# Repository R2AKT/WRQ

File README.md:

License addendum - https://github.com/R2AKT/WRQ/blob/main/Addendum.txt

# WRQ

Wait state insertion module. For Mega-80 (Mega-580) DIY 8-bit micro-computer - https://github.com/R2AKT/Mega-80.

Generation of a CPU module 'Wait' signal upon request from a slow device.

Status: Under testing.

Модуль задержки. Для самодельной 8-битной микро-ЭВМ - https://github.com/R2AKT/Mega-80.

Генерация по запросу от медленного устройства сигнала торможения процессорного модуля.

Статус: В стадии тестирования.

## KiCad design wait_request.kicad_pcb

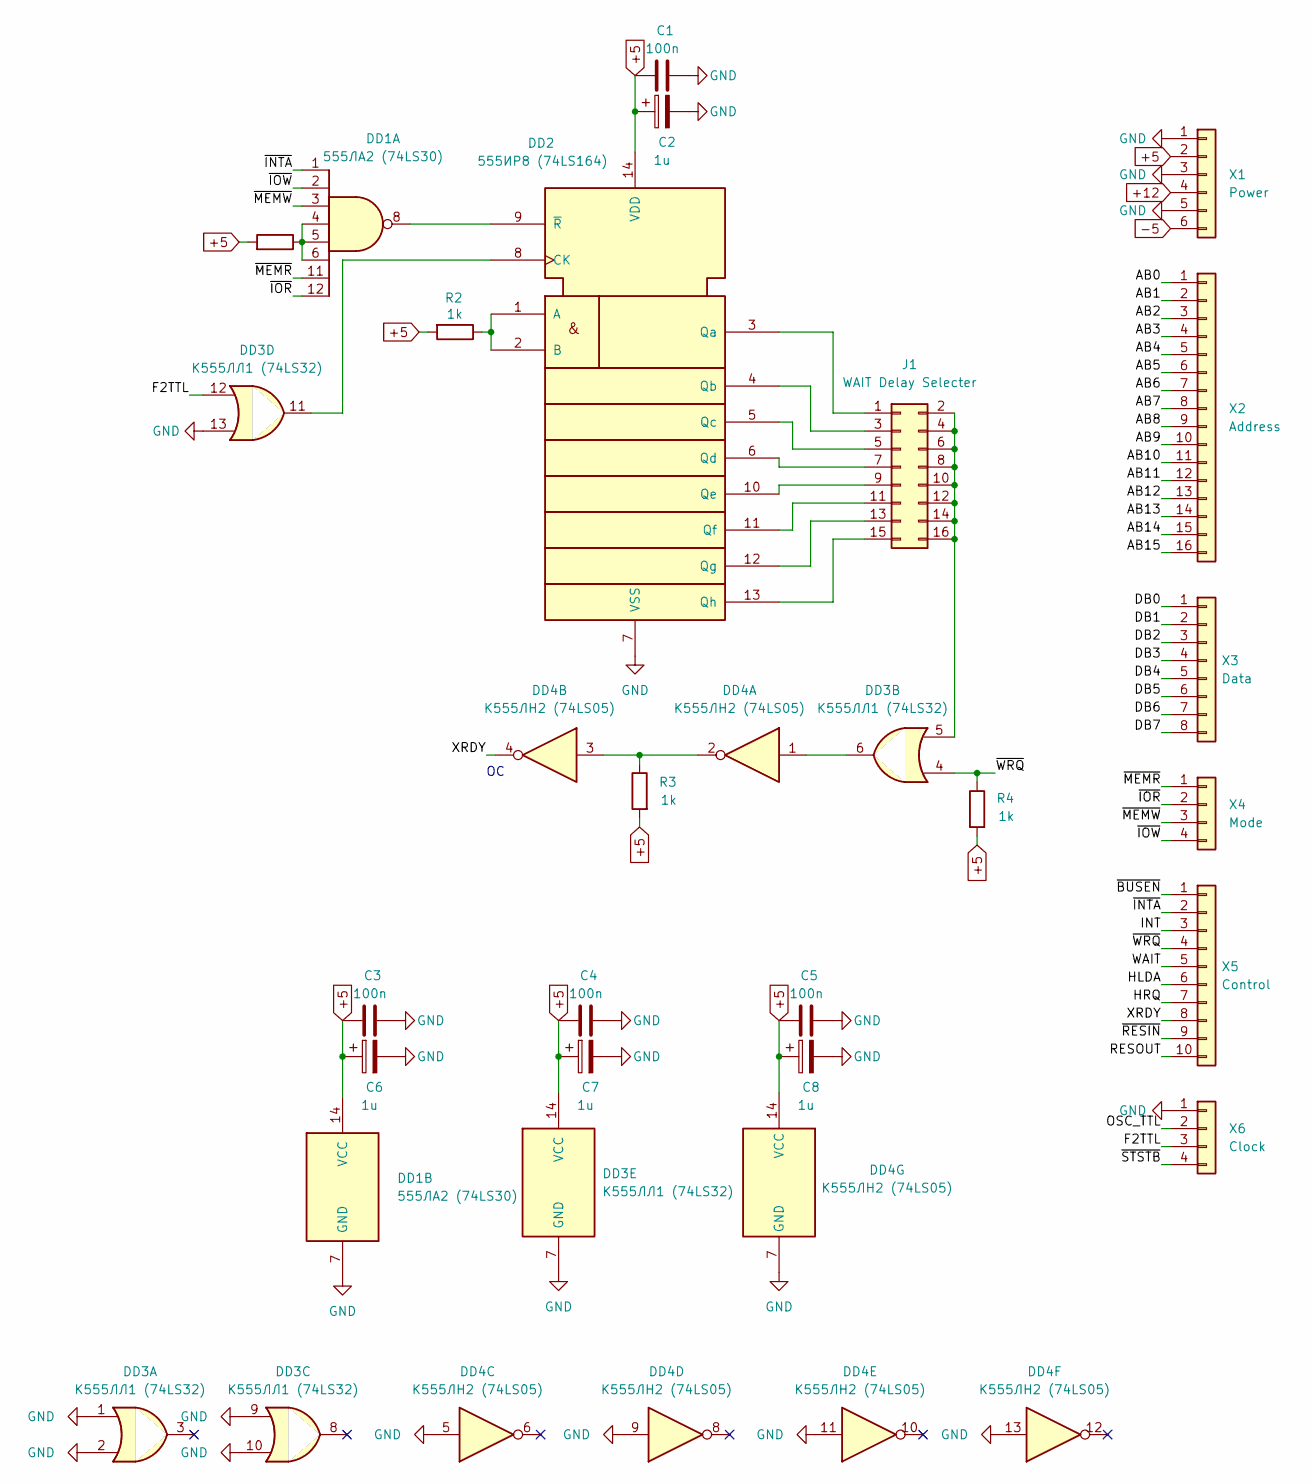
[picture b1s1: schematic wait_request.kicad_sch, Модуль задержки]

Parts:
C1, C3, C4, C5: 100n; C_0805_2012Metric_Pad1.18x1.45mm_HandSolder
C2, C6, C7, C8: 1u; CP_EIA-3216-18_Kemet-A_Pad1.58x1.35mm_HandSolder
DD1: 555ЛА2 (74LS30); DIP-14_W7.62mm_Socket_LongPads
DD2: 555ИР8 (74LS164); DIP-14_W7.62mm_Socket_LongPads
DD3: К555ЛЛ1 (74LS32); DIP-14_W7.62mm_Socket_LongPads
DD4: К555ЛН2 (74LS05); DIP-14_W7.62mm_Socket_LongPads
J1: WAIT Delay Selecter; PinHeader_2x08_P2.54mm_Vertical
R1, R2, R3, R4: 1k; R_0805_2012Metric_Pad1.20x1.40mm_HandSolder
X1: Power; PinHeader_1x06_P2.54mm_Vertical
X2: Address; PinHeader_1x16_P2.54mm_Vertical
X3: Data; PinHeader_1x08_P2.54mm_Vertical
X4: Mode; PinHeader_1x04_P2.54mm_Vertical
X5: Control; PinHeader_1x10_P2.54mm_Vertical
X6: Clock; PinHeader_1x04_P2.54mm_Vertical

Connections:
+5: C1.1, C2.1, C3.1, C4.1, C5.1, C6.1, C7.1, C8.1, DD1.14 (VCC), DD2.14 (VDD), DD3.14 (VCC), DD4.14 (VCC), R1.2, R2.2, R3.2, R4.2, X1.2
+12: X1.4
-5: X1.6
/AB0: X2.1
/AB1: X2.2
/AB2: X2.3
/AB3: X2.4
/AB4: X2.5
/AB5: X2.6
/AB6: X2.7
/AB7: X2.8
/AB8: X2.9
/AB9: X2.10
/AB10: X2.11
/AB11: X2.12
/AB12: X2.13
/AB13: X2.14
/AB14: X2.15
/AB15: X2.16
/DB0: X3.1
/DB1: X3.2
/DB2: X3.3
/DB3: X3.4
/DB4: X3.5
/DB5: X3.6
/DB6: X3.7
/DB7: X3.8
/F2TTL: DD3.12, X6.3
/HLDA: X5.6
/HRQ: X5.7
/INT: X5.3
/OSC_TTL: X6.2
/RESOUT: X5.10
/WAIT: X5.5
/XRDY: DD4.4, X5.8
/~BUSEN: X5.1
/~INTA: DD1.1, X5.2
/~IOR: DD1.12, X4.2
/~IOW: DD1.2, X4.4
/~MEMR: DD1.11, X4.1
/~MEMW: DD1.3, X4.3
/~RESIN: X5.9
/~STSTB: X6.4
/~WRQ: DD3.4, R4.1, X5.4
GND: C1.2, C2.2, C3.2, C4.2, C5.2, C6.2, C7.2, C8.2, DD1.7 (GND), DD2.7 (VSS), DD3.1, DD3.2, DD3.7 (GND), DD3.9, DD3.10, DD3.13, DD4.5, DD4.7 (GND), DD4.9, DD4.11, DD4.13, X1.1, X1.3, X1.5, X6.1
unnamed: DD1.4, DD1.5, DD1.6, R1.1
unnamed: DD2.1 (A), DD2.2 (B), R2.1
unnamed: DD2.8 (CK), DD3.11
unnamed: DD2.3 (Qa), J1.1
unnamed: DD2.4 (Qb), J1.3
unnamed: DD2.5 (Qc), J1.5
unnamed: DD2.6 (Qd), J1.7
unnamed: DD2.10 (Qe), J1.9
unnamed: DD2.11 (Qf), J1.11
unnamed: DD2.12 (Qg), J1.13
unnamed: DD2.13 (Qh), J1.15
unnamed: DD1.8, DD2.9 (~R)
unnamed: DD3.6, DD4.1
unnamed: DD4.2, DD4.3, R3.1
unnamed: DD3.5, J1.2, J1.4, J1.6, J1.8, J1.10, J1.12, J1.14, J1.16

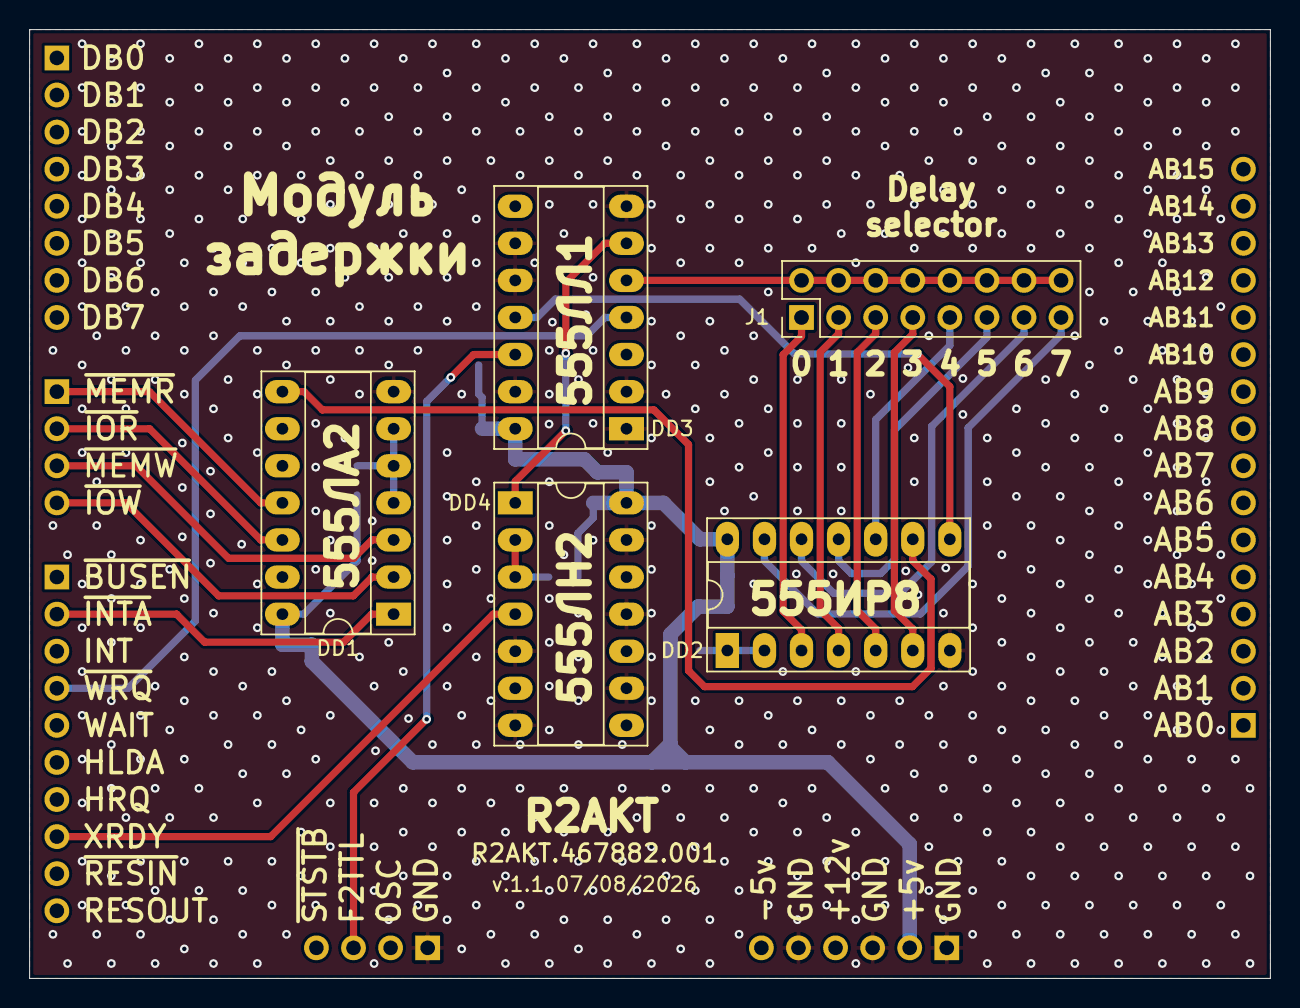
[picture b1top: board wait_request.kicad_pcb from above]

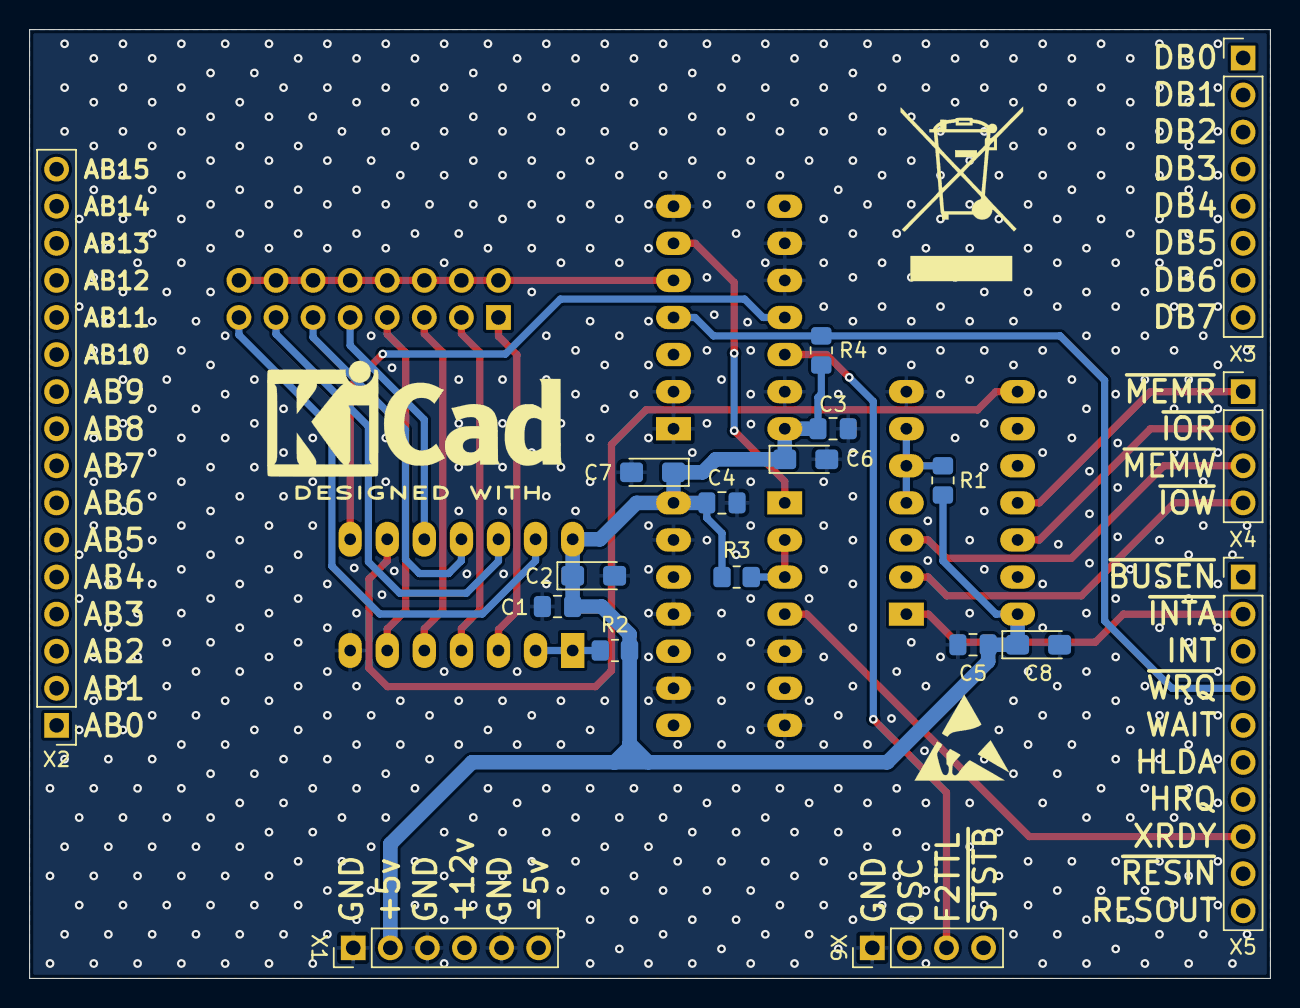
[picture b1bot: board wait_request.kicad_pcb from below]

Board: 2 copper layers, 85.0 x 65.0 mm, 23 parts (18 on the bottom side), 25 nets.

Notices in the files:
README.md:
License: MIT
